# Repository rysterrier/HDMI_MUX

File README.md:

# HDMI_MUX
 HDMI Switch

HDMI 2:1 Switch

MUX IC: TS3DV642A0RUAR

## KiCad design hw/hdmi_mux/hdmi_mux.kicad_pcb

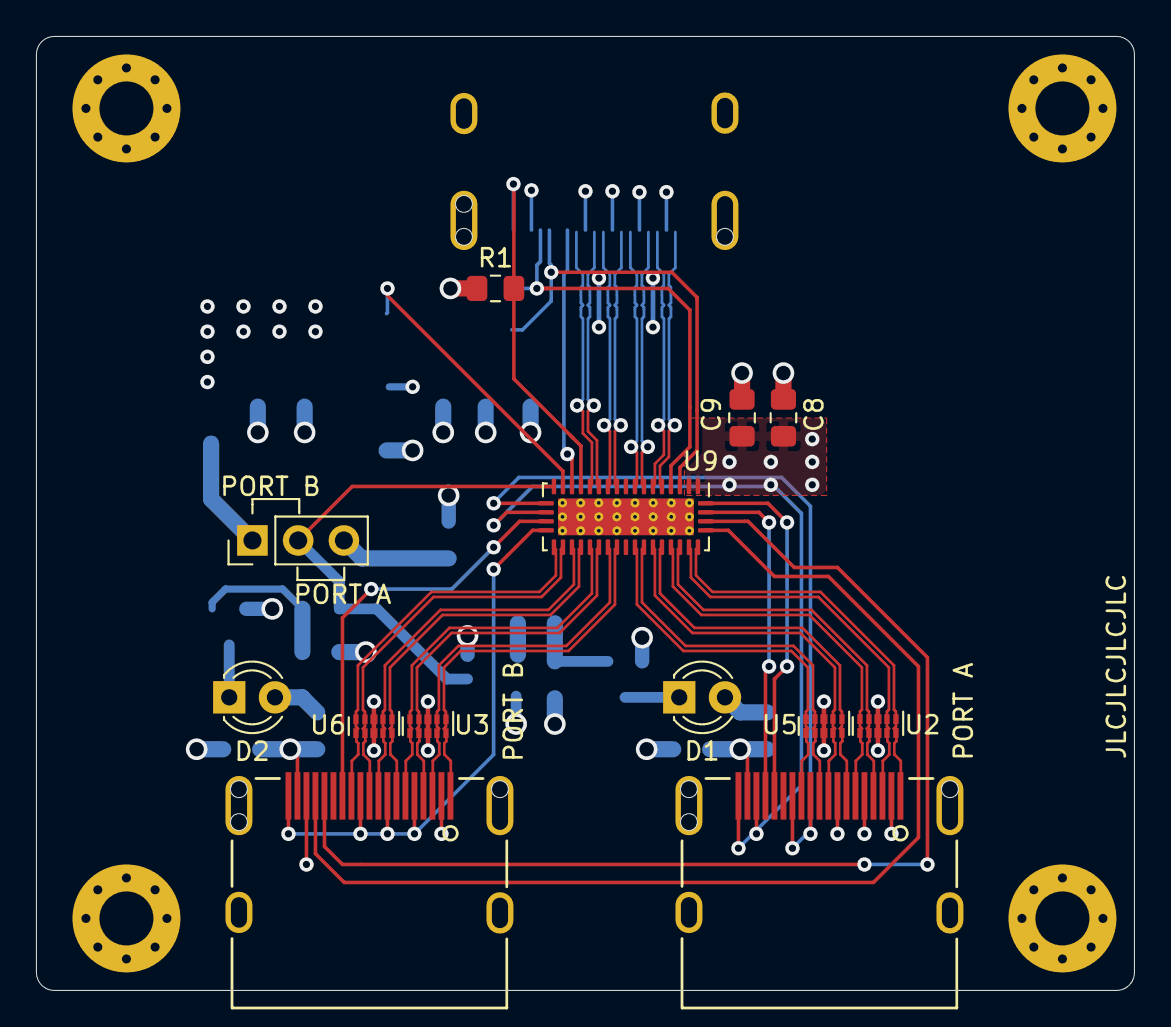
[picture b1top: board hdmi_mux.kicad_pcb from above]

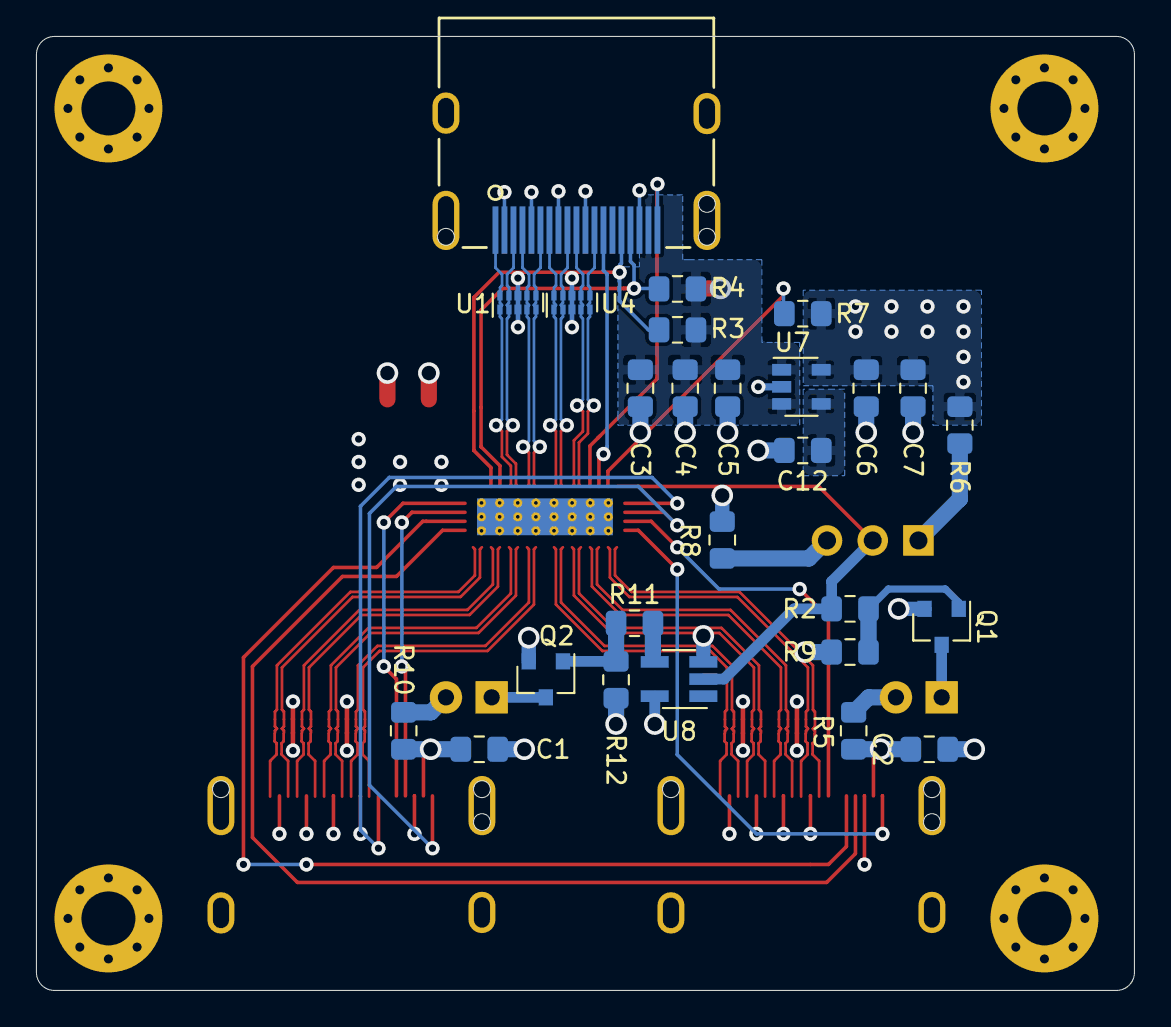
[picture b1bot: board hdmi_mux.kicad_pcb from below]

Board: 4 copper layers, 61.0 x 53.0 mm, 43 parts (26 on the bottom side), 53 nets.

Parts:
C1, C2, C3, C8: 0.1uF; C_0805_2012Metric_Pad1.15x1.40mm_HandSolder
C4: 10uF; C_0805_2012Metric_Pad1.15x1.40mm_HandSolder
C5: 1uF; C_0805_2012Metric_Pad1.15x1.40mm_HandSolder
C6: 2.2uF; C_0805_2012Metric_Pad1.15x1.40mm_HandSolder
C7: 4.7uF; C_0805_2012Metric_Pad1.15x1.40mm_HandSolder
C9: 0.01uF; C_0805_2012Metric_Pad1.15x1.40mm_HandSolder
C12: 10nF; C_0805_2012Metric_Pad1.15x1.40mm_HandSolder
D1, D2: 20mA Diode; LED_D3.0mm_FlatTop
H1, H2, H3, H4: MountingHole; MountingHole_3mm_Pad_Via
J1, J2, J3: HDMI_A; 47151-0002_MOLEX
Q1, Q2: IRLML0030; SOT-23
R1: 100k; R_0805_2012Metric_Pad1.15x1.40mm_HandSolder
R2, R11: 10; R_0805_2012Metric_Pad1.15x1.40mm_HandSolder
R3, R4: 2k; R_0805_2012Metric_Pad1.15x1.40mm_HandSolder
R5, R10: 200; R_0805_2012Metric_Pad1.15x1.40mm_HandSolder
R6, R7, R8: 10k; R_0805_2012Metric_Pad1.15x1.40mm_HandSolder
R9, R12: 1M; R_0805_2012Metric_Pad1.15x1.40mm_HandSolder
SW1: MTS-102 A-2; PinHeader_1x03_P2.54mm_Vertical
U1, U2, U3, U4, U5, U6: ESD224; USON-10_2.5x1.0mm_P0.5mm
U7: LP2985-3.3; SOT-23-5
U8: 74AHC1G04; SOT-23-5_HandSoldering
U9: TS3DV642A0RUAR; WQFN-42-1EP_3.5x9mm_P0.5mm_EP2.05x7.55mm_ThermalVias

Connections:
+3V3: C6.1, C7.1, C8.1, C9.1, R6.1, R7.1, U7.5, U8.5, U9.1, U9.2
+5V: C3.2, C4.1, C5.1, J1.18, R3.1, R4.1, U7.1, U7.3
/A_ACTIVE: C1.2, J2.18, R10.2
/B_ACTIVE: C2.2, J3.18, R5.2
CEC_A: J2.13, U9.18
CEC_B: J3.13, U9.20
CEC_C: J1.13, U9.15
D0_A_N: J2.12, U5.5, U5.6, U9.31
D0_A_P: J2.10, U5.4, U5.7, U9.32
D0_B_N: J3.12, U6.5, U6.6, U9.22
D0_B_P: J3.10, U6.4, U6.7, U9.23
D0_C_N: J1.12, U4.5, U4.6, U9.13
D0_C_P: J1.10, U4.4, U4.7, U9.12
D1_A_N: J2.9, U5.2, U5.9, U9.33
D1_A_P: J2.7, U5.1, U5.10, U9.34
D1_B_N: J3.9, U6.2, U6.9, U9.24
D1_B_P: J3.7, U6.1, U6.10, U9.25
D1_C_N: J1.9, U4.2, U4.9, U9.11
D1_C_P: J1.7, U4.1, U4.10, U9.10
D2_A_N: J2.6, U2.5, U2.6, U9.35
D2_A_P: J2.4, U2.4, U2.7, U9.36
D2_B_N: J3.6, U3.5, U3.6, U9.26
D2_B_P: J3.4, U3.4, U3.7, U9.27
D2_C_N: J1.6, U1.5, U1.6, U9.8
D2_C_P: J1.4, U1.4, U1.7, U9.7
D3_A_N: J2.3, U2.2, U2.9, U9.37
D3_A_P: J2.1, U2.1, U2.10, U9.38
D3_B_N: J3.3, U3.2, U3.9, U9.28
D3_B_P: J3.1, U3.1, U3.10, U9.29
D3_C_N: J1.3, U1.2, U1.9, U9.6
D3_C_P: J1.1, U1.1, U1.10, U9.5
GND: C1.1, C2.1, C3.1, C4.2, C5.2, C6.2, C7.2, C8.2, C9.2, C12.2, J1.2, J1.5, J1.8, J1.11, J1.17, J2.2, J2.5, J2.8, J2.11, J2.17, J3.2, J3.5, J3.8, J3.11, J3.17, Q1.2, Q2.2, R1.2, R8.2, R9.1, R12.1, U1.3, U1.8, U2.3, U2.8, U3.3, U3.8, U4.3, U4.8, U5.3, U5.8, U6.3, U6.8, U7.2, U8.3, U9.43
HPD_A: J2.19, U9.19
HPD_B: J3.19, U9.21
HPD_C: J1.19, R1.1, U9.14
unnamed: C12.1, U7.4
unnamed: D1.1, Q2.3
unnamed: D1.2, R10.1
unnamed: D2.1, Q1.3
unnamed: D2.2, R5.1
unnamed: Q1.1, R2.2, R9.2
unnamed: Q2.1, R11.2, R12.2
unnamed: R6.2, SW1.1
unnamed: R7.2, U9.16
unnamed: R8.1, SW1.3
unnamed: R11.1, U8.4
SCL_A: J2.15, U9.42
SCL_B: J3.15, U9.40
SCL_C: J1.15, R3.2, U9.3
SDA_A: J2.16, U9.41
SDA_B: J3.16, U9.39
SDA_C: J1.16, R4.2, U9.4
SOURCE_SEL: R2.1, SW1.2, U8.2, U9.17

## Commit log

2020-07-14 Initial commit
    Inital commit
    Schematics and PCB
    Layout probably needs clean up and checking
